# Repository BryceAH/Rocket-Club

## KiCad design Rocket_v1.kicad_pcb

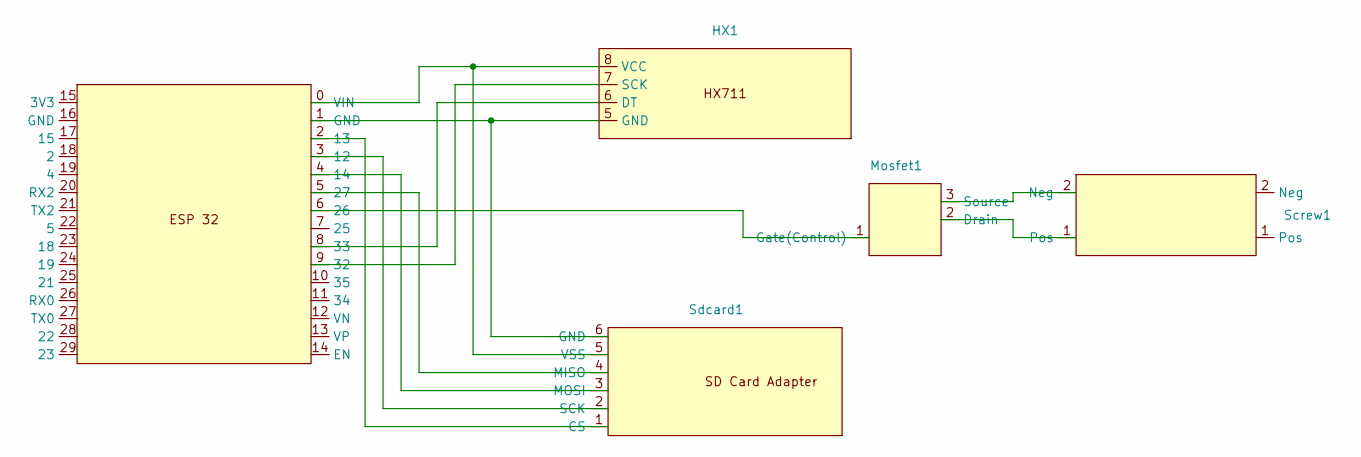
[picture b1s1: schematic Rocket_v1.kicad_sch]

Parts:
ESP1: Correct_Esp32
HX1: HX711 Bryce
Mosfet1: Mosfet
Screw1: 2 pin Screw term
Sdcard1: Sd adapter

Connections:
unnamed: ESP1.3 (12), Sdcard1.2 (SCK)
unnamed: ESP1.2 (13), Sdcard1.1 (CS)
unnamed: ESP1.4 (14), Sdcard1.3 (MOSI)
unnamed: ESP1.6 (26), Mosfet1.1 (Gate(Control))
unnamed: ESP1.5 (27), Sdcard1.4 (MISO)
unnamed: ESP1.9 (32), HX1.7 (SCK)
unnamed: ESP1.8 (33), HX1.6 (DT)
unnamed: ESP1.0 (VIN), HX1.8 (VCC), Sdcard1.5 (VSS)
unnamed: ESP1.1 (GND), HX1.5 (GND), Sdcard1.6 (GND)
unnamed: Mosfet1.2 (Drain), Screw1.1 (Pos)
unnamed: Mosfet1.3 (Source), Screw1.2 (Neg)

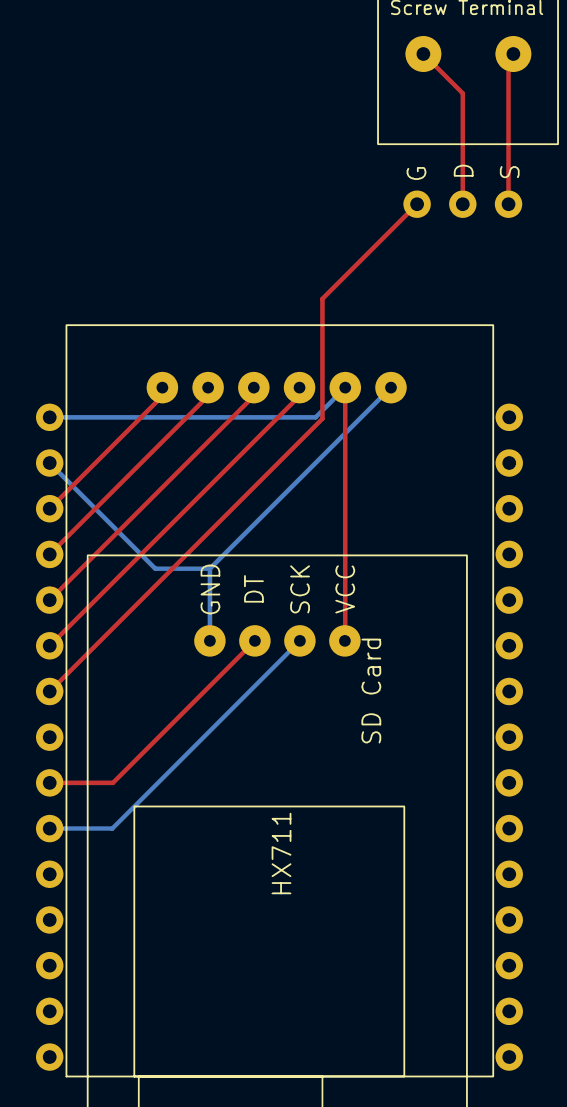
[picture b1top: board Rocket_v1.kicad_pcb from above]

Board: 2 copper layers, 5 parts (1 on the bottom side), 11 nets.

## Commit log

2024-02-06 Add files via upload
    Backup of Esp libraries.
